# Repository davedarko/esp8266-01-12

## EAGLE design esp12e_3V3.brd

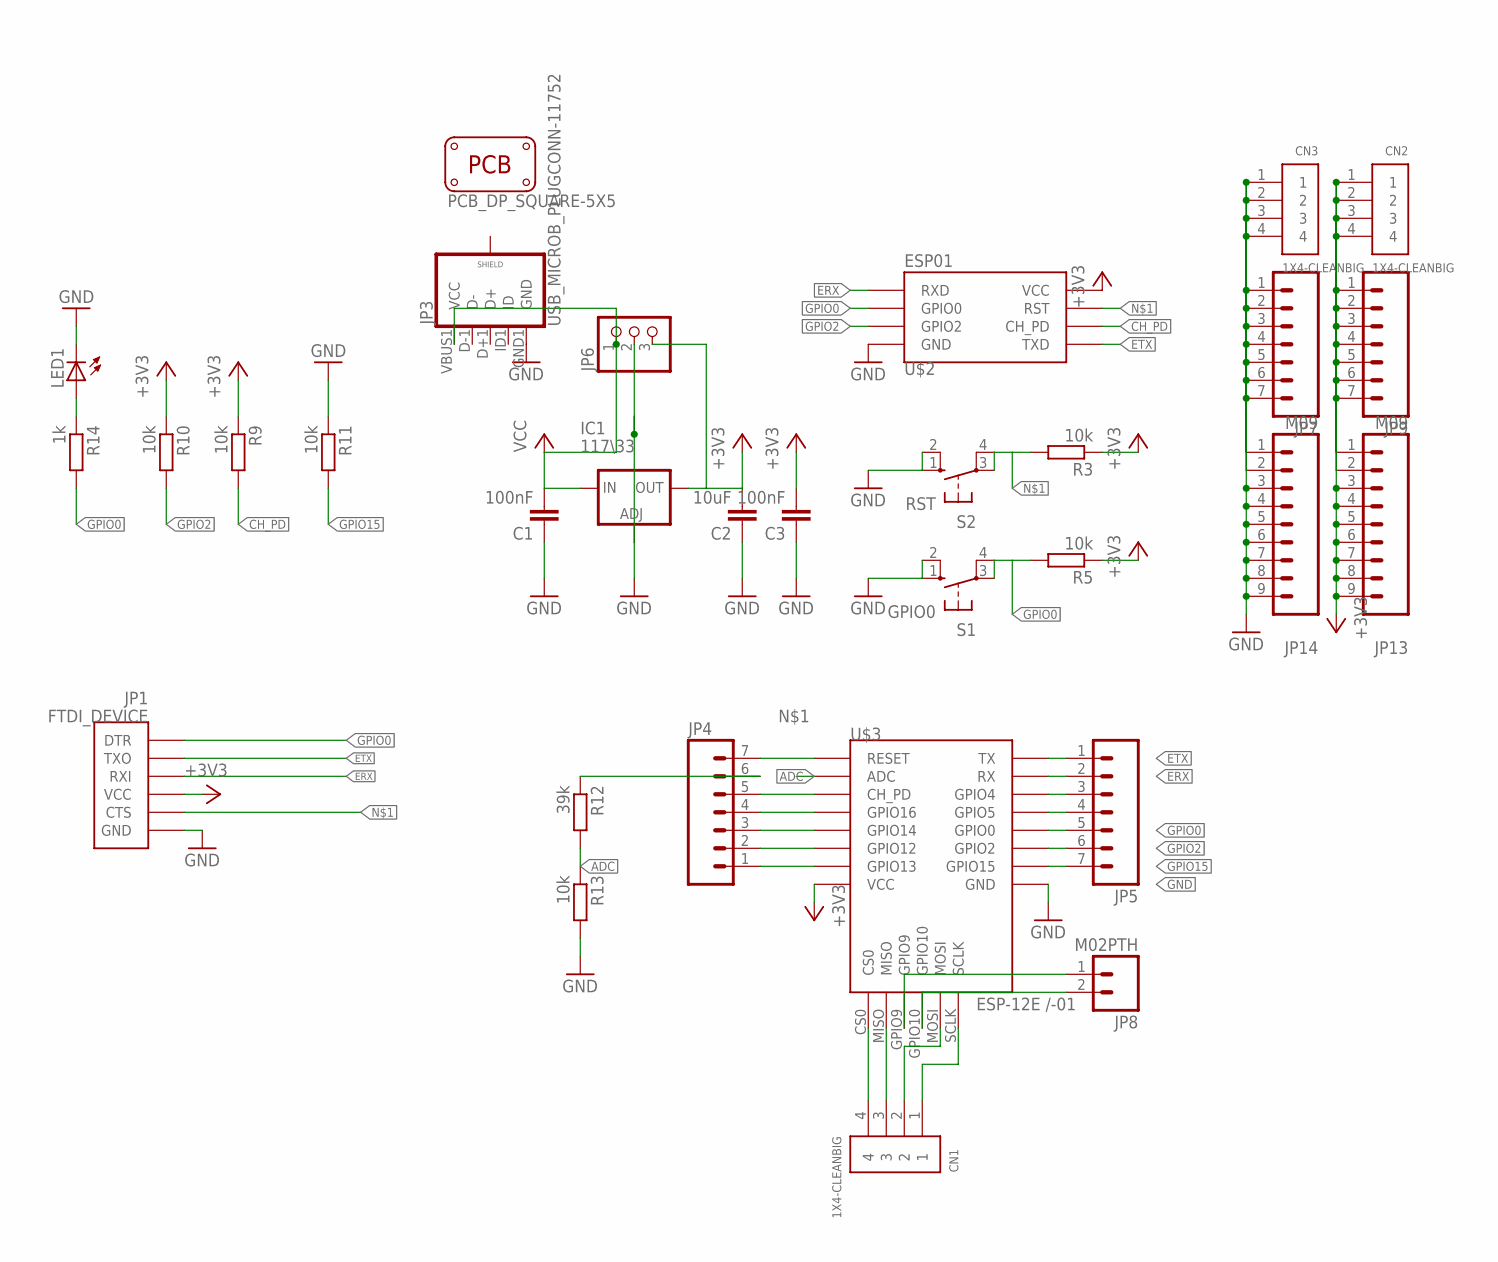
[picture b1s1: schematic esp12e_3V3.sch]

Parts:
C1, C3: 100nF; C1206
C2: 10uF; C1206
CN1, CN2, CN3: 1X4-CLEANBIG; 1X04-CLEANBIG
IC1: 117\33; SOT223
JP1: FTDI_DEVICE; FTDI_DEVICE_SIDE
JP3: USB_MICROB_PLUGCONN-11752; USB-B-MICRO-SMD_V03
JP4, JP5, JP7, JP9: M07; 1X07
JP6: PINHD-1X3; 1X03
JP8: M02PTH; 1X02
JP13, JP14: M09; 1X09
LED1: LEDSMT1206; 1206
PCB1: PCB_DP_SQUARE-5X5; DP5050_V1
R3, R5, R9, R10, R11, R13: 10k; M1206
R12: 39k; M1206
R14: 1k; M1206
S1: GPIO0; B3F-10XX
S2: RST; B3F-10XX
U$2: ESP01
U$3: ESP-12E /-01; ESP12E

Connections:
+3V3: C2.2, C3.2, CN2.1, CN2.2, CN2.3, CN2.4, IC1.4 (OUT), JP1.P$4 (VCC), JP6.3, JP9.1, JP9.2, JP9.3, JP9.4, JP9.5, JP9.6, JP9.7, JP13.1, JP13.2, JP13.3, JP13.4, JP13.5, JP13.6, JP13.7, JP13.8, JP13.9, R3.1, R5.1, R9.1, R10.1, U$2.VCC, U$3.VCC
ADC: R12.2, R13.1, U$3.ADC
CH_PD: JP4.5, R9.2, U$2.CH_PD, U$3.CH_PD
ERX: JP1.P$3 (RXI), JP5.2, U$2.RX (RXD), U$3.RX
ETX: JP1.P$2 (TXO), JP5.1, U$2.TX (TXD), U$3.TX
GND: C1.1, C2.1, C3.1, CN3.1, CN3.2, CN3.3, CN3.4, IC1.1 (ADJ), JP1.P$6 (GND), JP3.GND1 (GND), JP6.2, JP7.1, JP7.2, JP7.3, JP7.4, JP7.5, JP7.6, JP7.7, JP14.1, JP14.2, JP14.3, JP14.4, JP14.5, JP14.6, JP14.7, JP14.8, JP14.9, LED1.C, R11.1, R13.2, S1.1 (S), S1.2 (S1), S2.1 (S), S2.2 (S1), U$2.GND, U$3.GND
GPIO0: JP1.P$1 (DTR), JP5.5, R5.2, R14.2, S1.3, S1.4 (P1), U$2.GPIO0, U$3.GPIO0
GPIO2: JP5.6, R10.2, U$2.GPIO2, U$3.GPIO2
GPIO15: JP5.7, R11.2, U$3.GPIO15
unnamed: JP1.P$5 (CTS), JP4.7, R3.2, S2.3, S2.4 (P1), U$2.RST, U$3.RESET
unnamed: CN1.4, U$3.CS0
unnamed: JP4.1, U$3.GPIO13
unnamed: JP4.2, U$3.GPIO12
unnamed: JP4.3, U$3.GPIO14
unnamed: CN1.3, U$3.MISO
unnamed: JP4.4, U$3.GPIO16
unnamed: LED1.A, R14.1
unnamed: JP4.6, R12.1
unnamed: CN1.2, U$3.MOSI
unnamed: CN1.1, U$3.SCLK
unnamed: JP5.4, U$3.GPIO5
unnamed: JP5.3, U$3.GPIO4
unnamed: JP8.1, U$3.GPIO9
unnamed: JP8.2, U$3.GPIO10
VCC: C1.2, IC1.3 (IN), JP3.VBUS1 (VCC), JP6.1

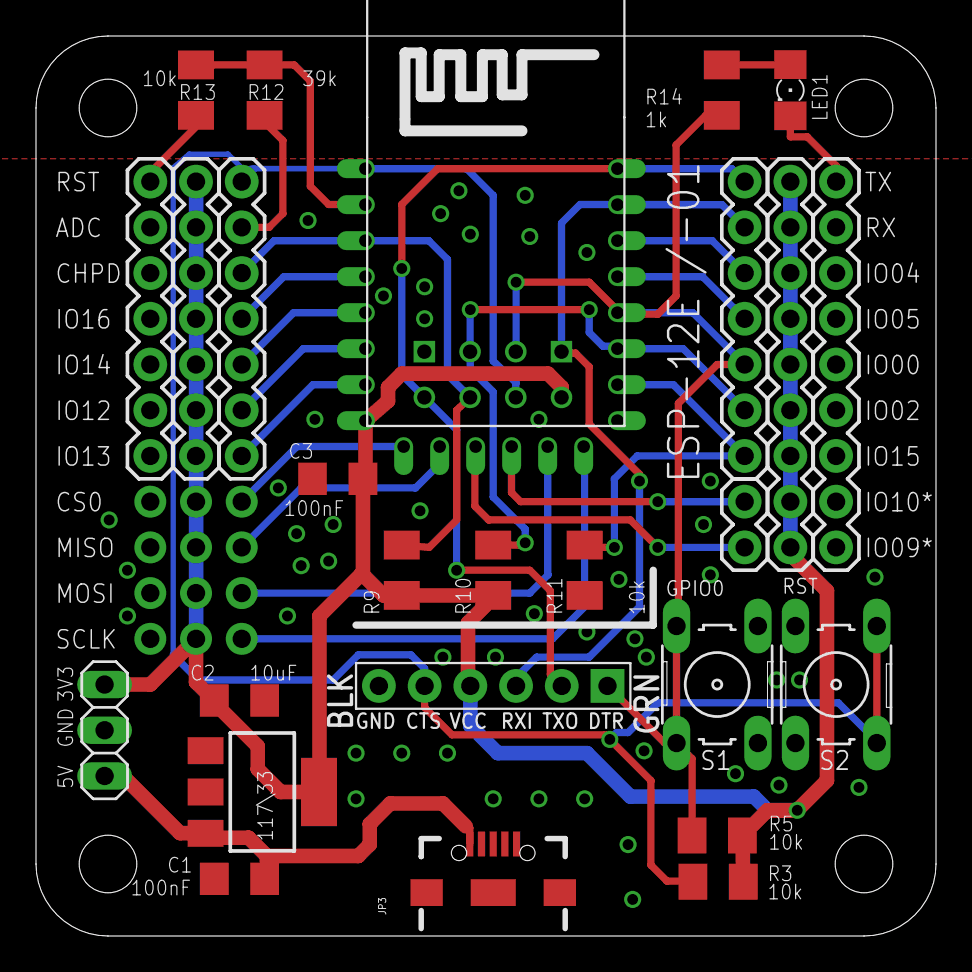
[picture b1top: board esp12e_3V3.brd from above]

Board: 2 copper layers, 50.0 x 50.0 mm, 31 parts (0 on the bottom side), 25 nets.

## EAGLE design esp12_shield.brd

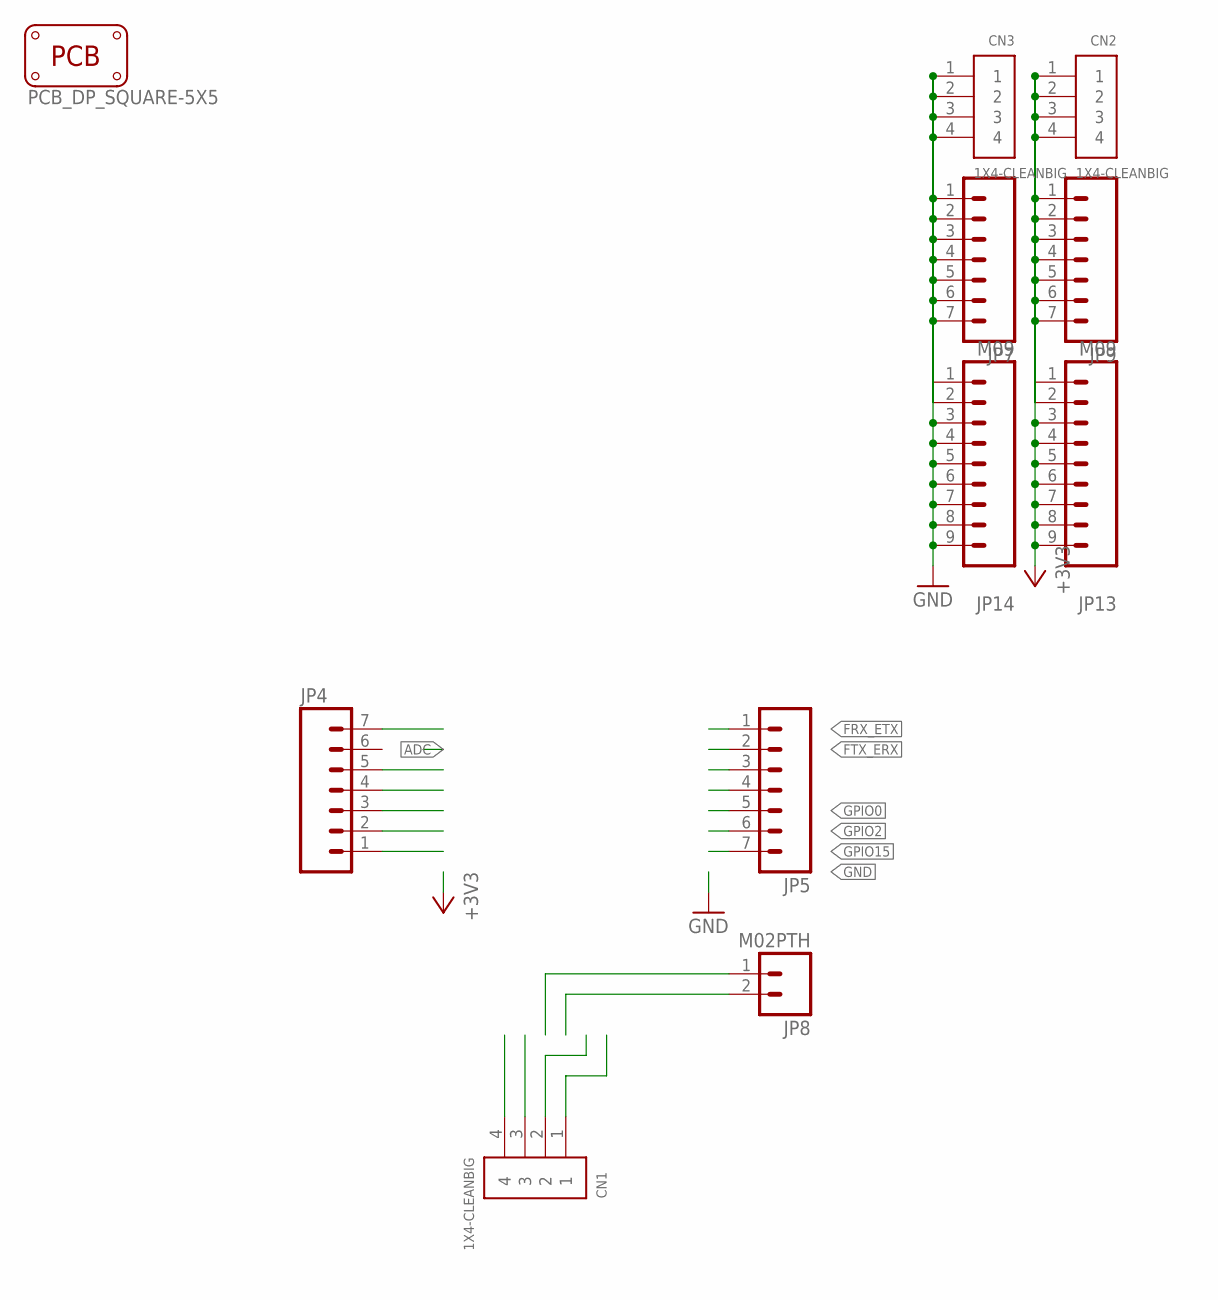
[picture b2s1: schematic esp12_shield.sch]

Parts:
CN1, CN2, CN3: 1X4-CLEANBIG; 1X04-CLEANBIG
JP4, JP5, JP7, JP9: M07; 1X07
JP8: M02PTH; 1X02
JP13, JP14: M09; 1X09
PCB1: PCB_DP_SQUARE-5X5; DP5050_V1

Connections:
+3V3: CN2.1, CN2.2, CN2.3, CN2.4, JP9.1, JP9.2, JP9.3, JP9.4, JP9.5, JP9.6, JP9.7, JP13.1, JP13.2, JP13.3, JP13.4, JP13.5, JP13.6, JP13.7, JP13.8, JP13.9
CH_PD: JP4.5
FRX_ETX: JP5.1
FTX_ERX: JP5.2
GND: CN3.1, CN3.2, CN3.3, CN3.4, JP7.1, JP7.2, JP7.3, JP7.4, JP7.5, JP7.6, JP7.7, JP14.1, JP14.2, JP14.3, JP14.4, JP14.5, JP14.6, JP14.7, JP14.8, JP14.9
GPIO0: JP5.5
GPIO2: JP5.6
GPIO15: JP5.7

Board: 2 copper layers, 11 parts (0 on the bottom side), 2 nets, no tracks yet.

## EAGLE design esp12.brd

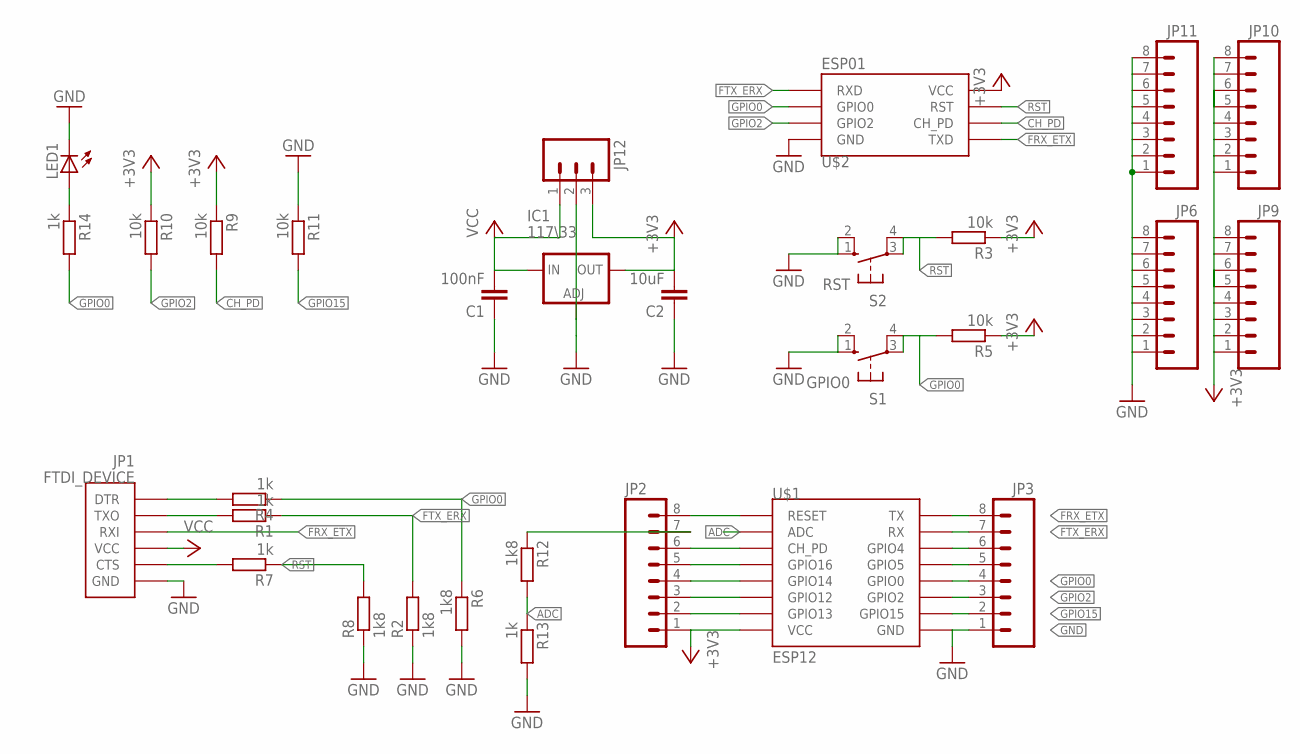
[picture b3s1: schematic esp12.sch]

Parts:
C1: 100nF; C1206
C2: 10uF; C1206
IC1: 117\33; SOT223
JP1: FTDI_DEVICE; FTDI_DEVICE_SIDE
JP2, JP3, JP6, JP9, JP10, JP11: M08; 1X08_ROUND
JP12: M03PTH; 1X03
LED1: LEDSMT1206; 1206
R1, R4, R7, R13, R14: 1k; M1206
R2, R6, R8, R12: 1k8; M1206
R3, R5, R9, R10, R11: 10k; M1206
S1: GPIO0; B3F-10XX
S2: RST; B3F-10XX
U$1: ESP12
U$2: ESP01

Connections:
+3V3: C2.2, IC1.4 (OUT), JP2.1, JP9.1, JP9.2, JP9.3, JP9.4, JP9.5, JP9.6, JP9.7, JP9.8, JP10.1, JP10.2, JP10.3, JP10.4, JP10.5, JP10.6, JP10.7, JP10.8, JP12.3, R3.1, R5.1, R9.1, R10.1, U$1.VCC, U$2.VCC
ADC: R12.2, R13.1, U$1.ADC
CH_PD: JP2.6, R9.2, U$1.CH_PD, U$2.CH_PD
FRX_ETX: JP1.P$3 (RXI), JP3.8, U$1.TX, U$2.TX (TXD)
FTX_ERX: JP3.7, R1.1, R2.2, U$1.RX, U$2.RX (RXD)
GND: C1.1, C2.1, IC1.1 (ADJ), JP1.P$6 (GND), JP3.1, JP6.1, JP6.2, JP6.3, JP6.4, JP6.5, JP6.6, JP6.7, JP6.8, JP11.1, JP11.2, JP11.3, JP11.4, JP11.5, JP11.6, JP11.7, JP11.8, JP12.2, LED1.C, R2.1, R6.2, R8.1, R11.1, R13.2, S1.1 (S), S1.2 (S1), S2.1 (S), S2.2 (S1), U$1.GND, U$2.GND
GPIO0: JP3.4, R4.1, R5.2, R6.1, R14.2, S1.3, S1.4 (P1), U$1.GPIO0, U$2.GPIO0
GPIO2: JP3.3, R10.2, U$1.GPIO2, U$2.GPIO2
GPIO15: JP3.2, R11.2, U$1.GPIO15
unnamed: JP1.P$5 (CTS), R7.2
unnamed: JP1.P$2 (TXO), R1.2
unnamed: JP2.2, U$1.GPIO13
unnamed: JP2.3, U$1.GPIO12
unnamed: JP2.4, U$1.GPIO14
unnamed: JP1.P$1 (DTR), R4.2
unnamed: JP2.5, U$1.GPIO16
unnamed: LED1.A, R14.1
unnamed: JP2.7, R12.1
unnamed: JP3.5, U$1.GPIO5
unnamed: JP3.6, U$1.GPIO4
RST: JP2.8, R3.2, R7.1, R8.2, S2.3, S2.4 (P1), U$1.RESET, U$2.RST
VCC: C1.2, IC1.3 (IN), JP1.P$4 (VCC), JP12.1

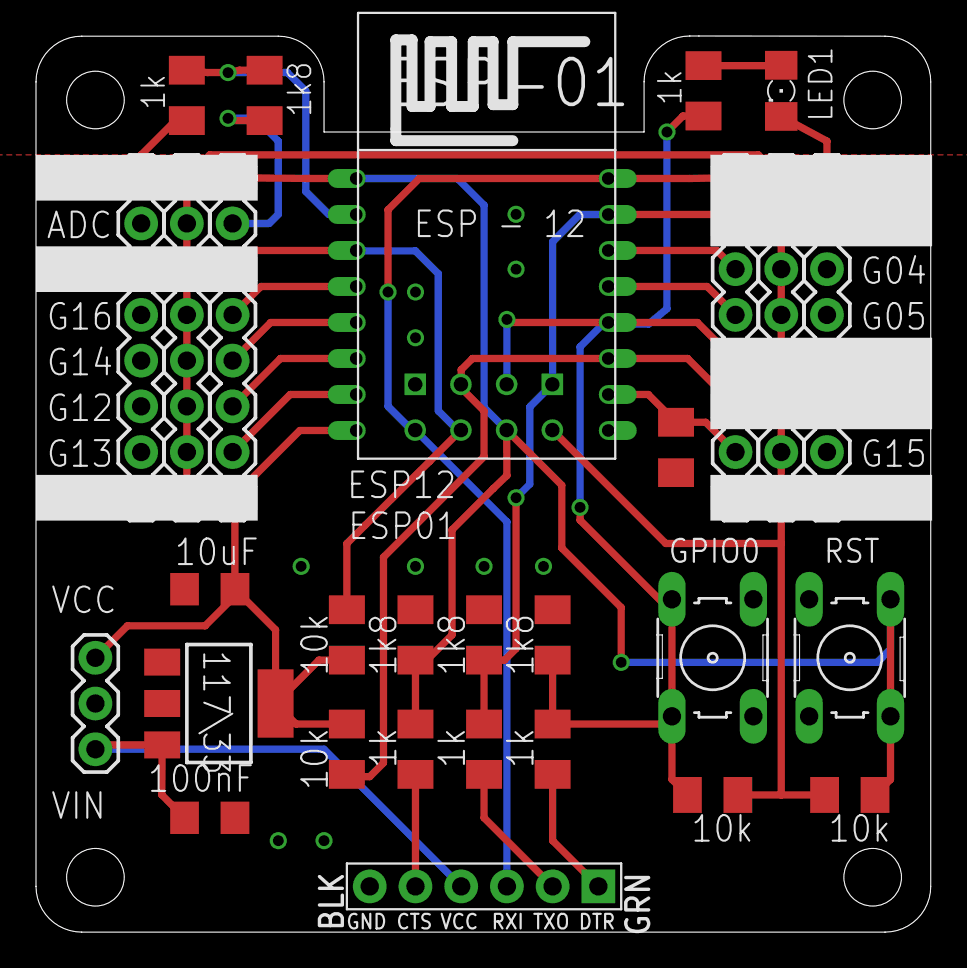
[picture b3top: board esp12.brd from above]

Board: 2 copper layers, 49.7 x 49.8 mm, 30 parts (0 on the bottom side), 22 nets.

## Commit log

2015-05-16 first draft
2015-05-16 gitignore and ADC 5V to 1.8V conversion
2015-05-16 LED for GPIO0 added
2015-05-16 added hackaday swag
2015-05-16 changed fonts and layers
2015-05-19 I don't know. Stuffy stuff.
2015-05-19 esp12e boards added
2015-05-20 ISP AVR header - may be changed again
2015-05-29 hackaday swag
2015-06-01 100nF because of regulator
2015-06-01 3.3V Version
2015-07-18 esp12e revision
2015-07-18 layout
2015-07-18 missing 100nF label
2015-08-22 shield added
2015-08-24 moved 5V header, ftdi and added micro usbfootprint
2015-08-26 moved stuff
2015-10-19 removed "antenna" - wire on pcb and pulled usb
2016-08-12 kitnic.it stuff
2016-08-12 csv to tsv
2016-08-12 nvrmnd
2016-08-12 test
2016-08-12 makes sense now, kitnic?

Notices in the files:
parts and their libraries:
SparkFun-Connectors: Licensing: Creative Commons ShareAlike 4.0 International - https://creativecommons.org/licenses/by-sa/4.0
